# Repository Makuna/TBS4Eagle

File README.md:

# TBS4Eagle
Arduino Throttle Body Sync Shield Eagle Files.

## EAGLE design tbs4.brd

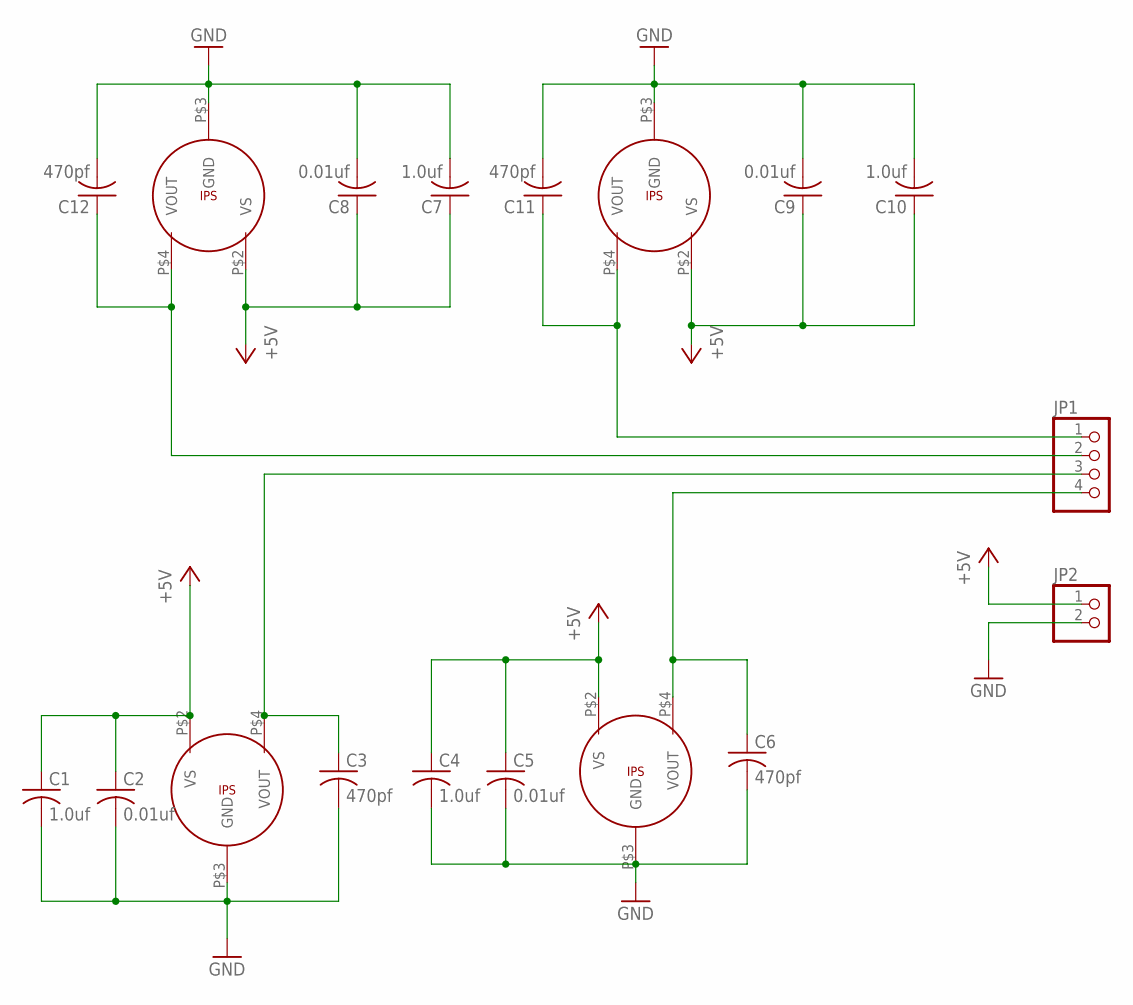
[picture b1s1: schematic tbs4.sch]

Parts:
C1, C4, C7, C10: 1.0uf; C0603
C2, C5, C8, C9: 0.01uf; C0603
C3, C6, C11, C12: 470pf; C0603
IPS1, IPS2, IPS3, IPS4: MPXV5050VC6T1; SOP-CASE-482A
JP1: PINHD-1X4; 1X04
JP2: PINHD-1X2; 1X02

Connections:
+5V: C1.1, C2.1, C4.1, C5.1, C7.1, C8.1, C9.1, C10.1, IPS1.P$2 (VS), IPS2.P$2 (VS), IPS3.P$2 (VS), IPS4.P$2 (VS), JP2.1
GND: C1.2, C2.2, C3.2, C4.2, C5.2, C6.2, C7.2, C8.2, C9.2, C10.2, C11.2, C12.2, IPS1.P$3 (GND), IPS2.P$3 (GND), IPS3.P$3 (GND), IPS4.P$3 (GND), JP2.2
OUTPUT1: C6.1, IPS4.P$4 (VOUT), JP1.4
OUTPUT2: C3.1, IPS3.P$4 (VOUT), JP1.3
OUTPUT3: C12.1, IPS2.P$4 (VOUT), JP1.2
OUTPUT4: C11.1, IPS1.P$4 (VOUT), JP1.1

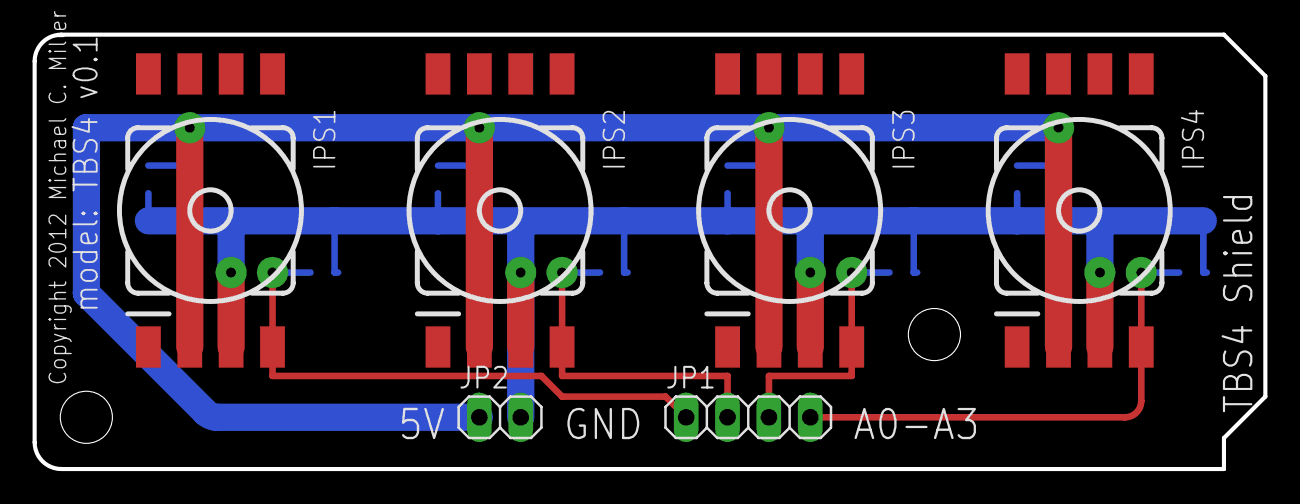
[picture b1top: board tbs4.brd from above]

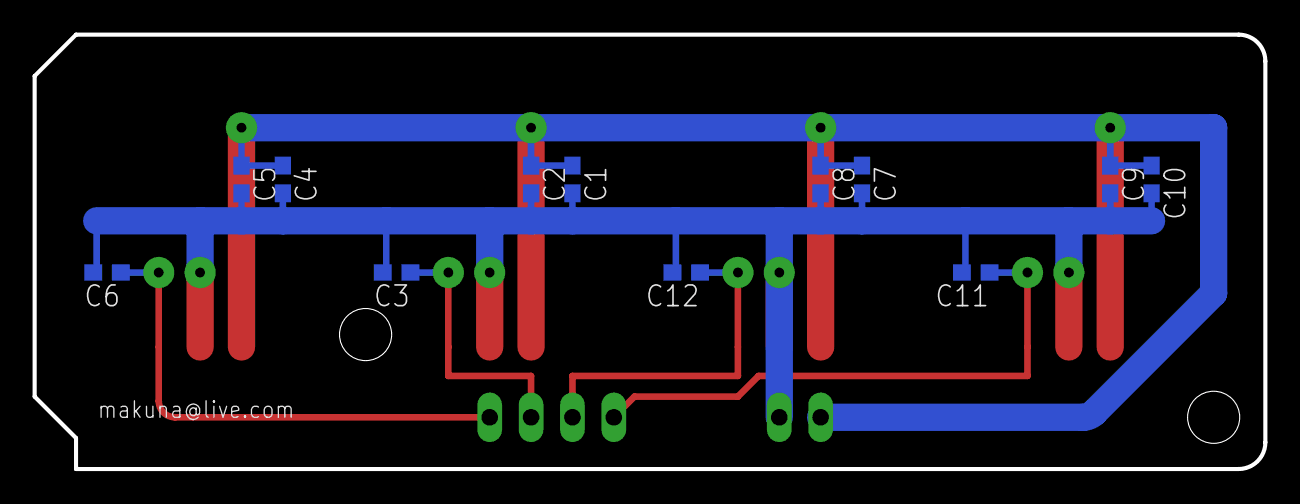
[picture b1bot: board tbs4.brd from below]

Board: 2 copper layers, 75.6 x 26.7 mm, 18 parts (12 on the bottom side), 6 nets.

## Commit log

2015-01-19 :octocat: Added .gitattributes & .gitignore files
2015-01-19 Throttle Body Sync Arduino Shield Schematic Files

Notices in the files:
tbs4.brd:
Copyright 2012 Michael C. Miller
